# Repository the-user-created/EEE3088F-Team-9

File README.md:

# EEE3088F 2022 HAT Project

# License
[Creative Commons Attribution 4.0 International license](https://choosealicense.com/licenses/cc-by-4.0/)

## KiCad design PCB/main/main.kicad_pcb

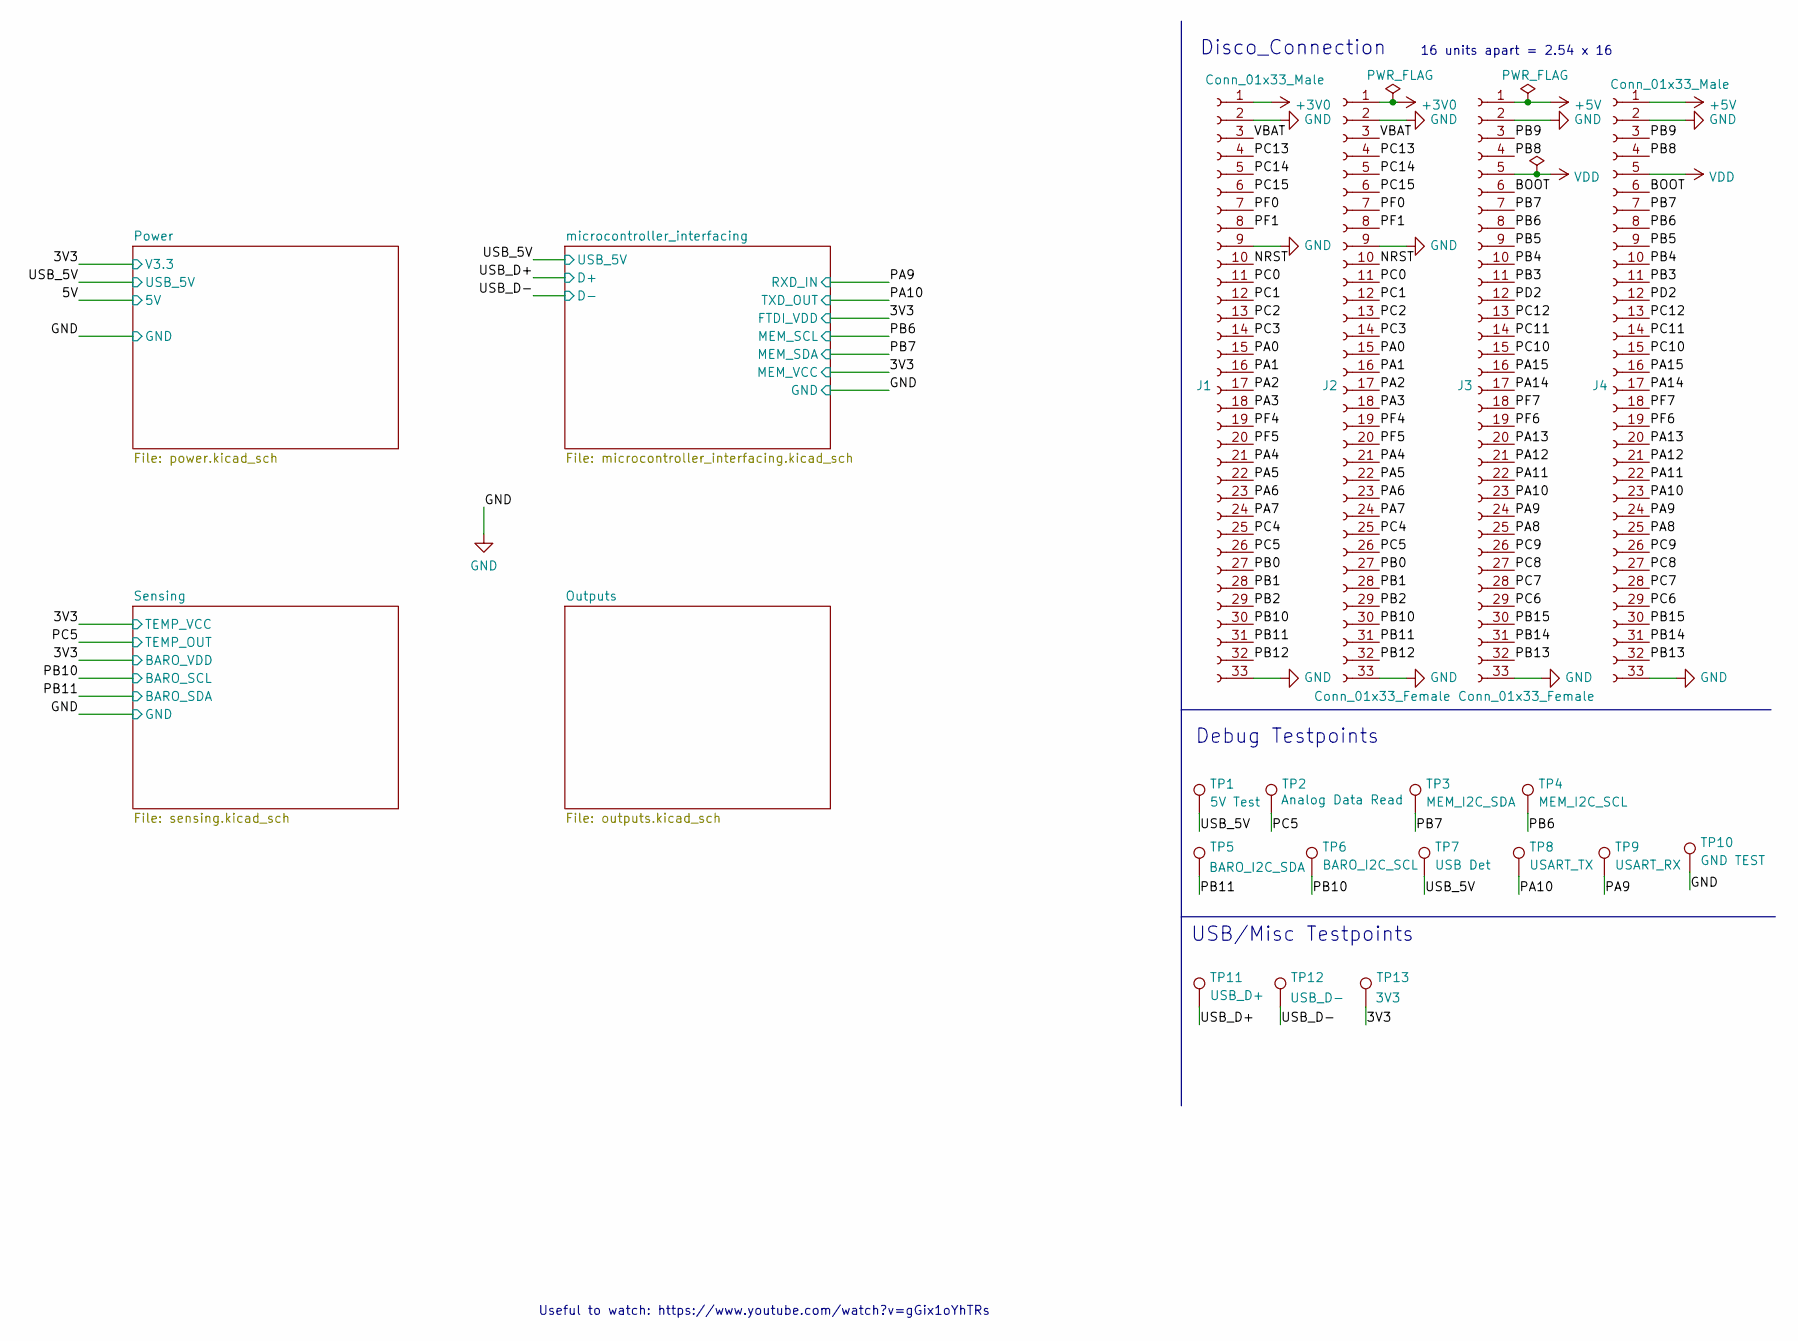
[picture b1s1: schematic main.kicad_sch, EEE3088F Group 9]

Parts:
J1, J4: Conn_01x33_Male; PinHeader_1x33_P2.54mm_Vertical
J2, J3: Conn_01x33_Female; PinSocket_1x33_P2.54mm_Vertical
TP1: 5V Test; TestPoint_Pad_2.5x2.5mm
TP2: Analog Data Read; TestPoint_Pad_2.5x2.5mm
TP3: MEM_I2C_SDA; TestPoint_Pad_2.5x2.5mm
TP4: MEM_I2C_SCL; TestPoint_Pad_2.5x2.5mm
TP5: BARO_I2C_SDA; TestPoint_Pad_2.5x2.5mm
TP6: BARO_I2C_SCL; TestPoint_Pad_2.5x2.5mm
TP7: USB Det; TestPoint_Pad_2.5x2.5mm
TP8: USART_TX; TestPoint_Pad_2.5x2.5mm
TP9: USART_RX; TestPoint_Pad_2.5x2.5mm
TP10: GND TEST; TestPoint_Pad_2.5x2.5mm
TP11: USB_D+; TestPoint_Pad_2.5x2.5mm
TP12: USB_D-; TestPoint_Pad_2.5x2.5mm
TP13: 3V3; TestPoint_Pad_2.5x2.5mm

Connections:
+3V0: J1.1, J2.1
+5V: J3.1, J4.1
/3V3: TP13.1; also elsewhere on the board
/BOOT: J3.6, J4.6
/NRST: J1.10, J2.10
/PA0: J1.15, J2.15
/PA1: J1.16, J2.16
/PA2: J1.17, J2.17
/PA3: J1.18, J2.18
/PA4: J1.21, J2.21
/PA5: J1.22, J2.22
/PA6: J1.23, J2.23
/PA7: J1.24, J2.24
/PA8: J3.25, J4.25
/PA9: J3.24, J4.24, TP9.1; also elsewhere on the board
/PA10: J3.23, J4.23, TP8.1; also elsewhere on the board
/PA11: J3.22, J4.22
/PA12: J3.21, J4.21
/PA13: J3.20, J4.20
/PA14: J3.17, J4.17
/PA15: J3.16, J4.16
/PB0: J1.27, J2.27
/PB1: J1.28, J2.28
/PB2: J1.29, J2.29
/PB3: J3.11, J4.11
/PB4: J3.10, J4.10
/PB5: J3.9, J4.9
/PB6: J3.8, J4.8, TP4.1; also elsewhere on the board
/PB7: J3.7, J4.7, TP3.1; also elsewhere on the board
/PB8: J3.4, J4.4
/PB9: J3.3, J4.3
/PB10: J1.30, J2.30, TP6.1; also elsewhere on the board
/PB11: J1.31, J2.31, TP5.1; also elsewhere on the board
/PB12: J1.32, J2.32
/PB13: J3.32, J4.32
/PB14: J3.31, J4.31
/PB15: J3.30, J4.30
/PC0: J1.11, J2.11
/PC1: J1.12, J2.12
/PC2: J1.13, J2.13
/PC3: J1.14, J2.14
/PC4: J1.25, J2.25
/PC5: J1.26, J2.26, TP2.1; also elsewhere on the board
/PC6: J3.29, J4.29
/PC7: J3.28, J4.28
/PC8: J3.27, J4.27
/PC9: J3.26, J4.26
/PC10: J3.15, J4.15
/PC11: J3.14, J4.14
/PC12: J3.13, J4.13
/PC13: J1.4, J2.4
/PC14: J1.5, J2.5
/PC15: J1.6, J2.6
/PD2: J3.12, J4.12
/PF0: J1.7, J2.7
/PF1: J1.8, J2.8
/PF4: J1.19, J2.19
/PF5: J1.20, J2.20
/PF6: J3.19, J4.19
/PF7: J3.18, J4.18
/USB_5V: TP1.1, TP7.1; also elsewhere on the board
/USB_D+: TP11.1; also elsewhere on the board
/USB_D-: TP12.1; also elsewhere on the board
/VBAT: J1.3, J2.3
GND: J1.2, J1.9, J1.33, J2.2, J2.9, J2.33, J3.2, J3.33, J4.2, J4.33, TP10.1; also elsewhere on the board
VDD: J3.5, J4.5

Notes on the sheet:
USB/Misc Testpoints
Useful to watch: https://www.youtube.com/watch?v=gGix1oYhTRs
16 units apart = 2.54 x 16
Disco_Connection
Debug Testpoints

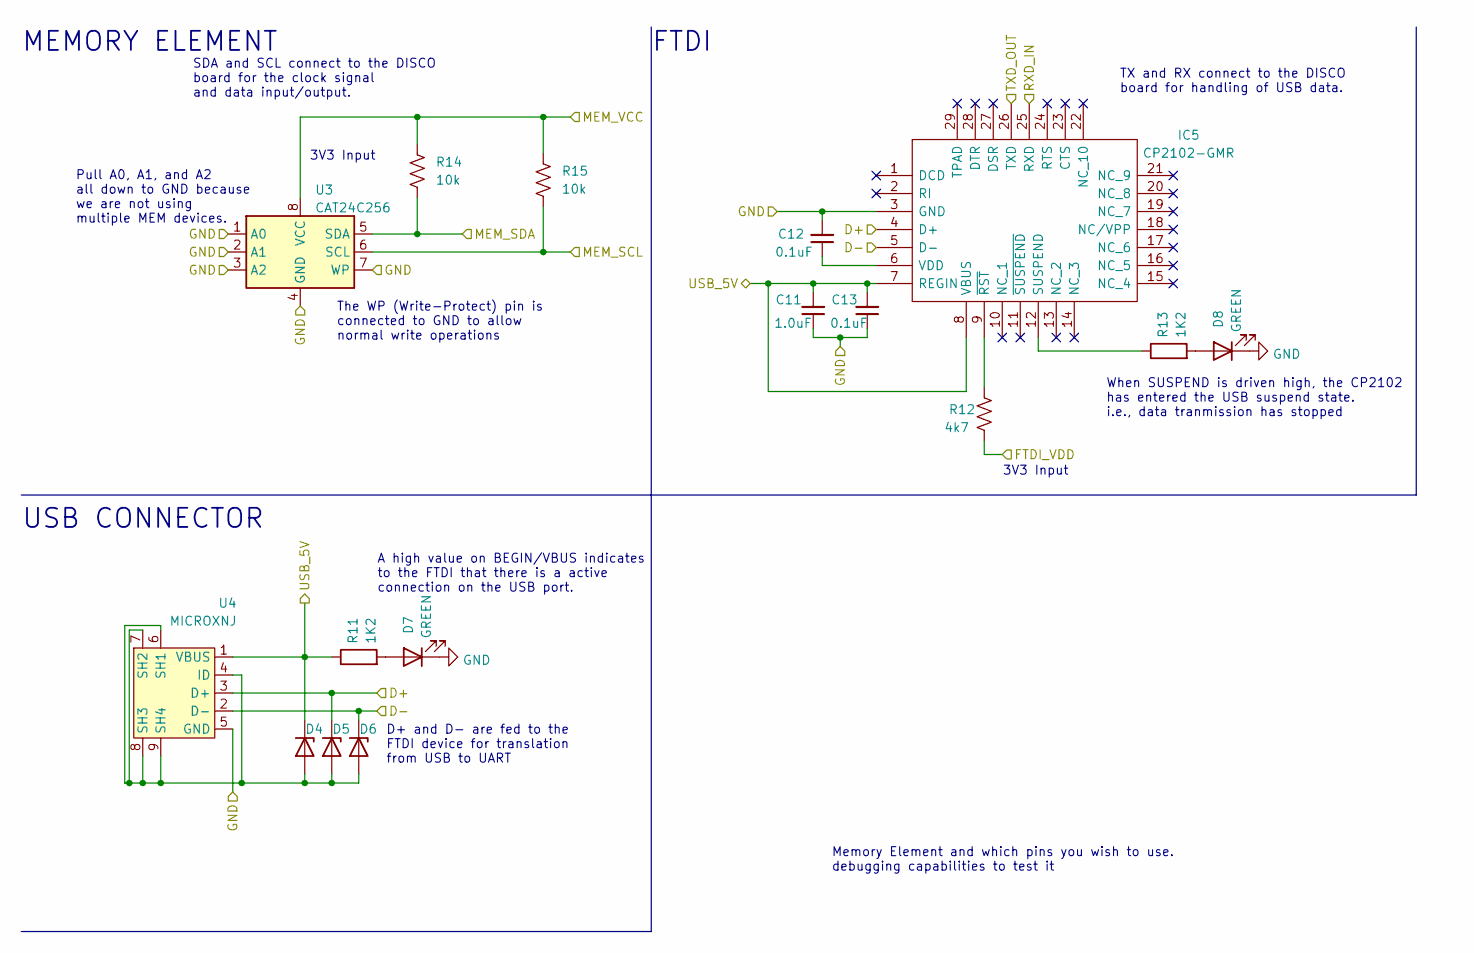
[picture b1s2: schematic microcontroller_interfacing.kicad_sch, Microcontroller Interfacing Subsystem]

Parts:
C11: 1.0uF; CAPC1608X90N; LCSC C15849
C12, C13: 0.1uF; CAPC1005X55N; LCSC C1525
D4, D5, D6: ZMMxx; LL-34_L3.5-W1.5-RD; LCSC C8056
D7, D8: GREEN; LEDC1608X50N; LCSC C72043
IC5: CP2102-GMR; QFN50P500X500X100-29N-D; Manufacturer_Part_Number CP2102-GMR; Mouser Part Number 634-CP2102-GMR
R11, R13: 1K2; RESC1608X55N; LCSC C22765
R12: 4k7; RESC1608X55N; LCSC C23162
R14, R15: 10k; R0603; LCSC C25804
U3: CAT24C256; SOIC127P600X175-8N; LCSC C6482
U4: MICROXNJ; MICRO-USB-SMD_MICROXNJ; LCSC C404969

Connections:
/3V3: R12.1, R14.1, R15.1, U3.8 (VCC); also elsewhere on the board
/PA9: IC5.25 (RXD); also elsewhere on the board
/PA10: IC5.26 (TXD); also elsewhere on the board
/PB6: R15.2, U3.6 (SCL); also elsewhere on the board
/PB7: R14.2, U3.5 (SDA); also elsewhere on the board
/USB_5V: C11.2, C13.2, D4.1 (K), IC5.7 (REGIN), IC5.8 (VBUS), R11.1, U4.1 (VBUS); also elsewhere on the board
/USB_D+: D5.1 (K), IC5.4 (D+), U4.3 (D+); also elsewhere on the board
/USB_D-: D6.1 (K), IC5.5 (D-), U4.2 (D-); also elsewhere on the board
GND: C11.1, C12.2, C13.1, D7.1 (K), D8.1 (K), IC5.3 (GND), U3.1 (A0), U3.2 (A1), U3.3 (A2), U3.4 (GND), U3.7 (WP), U4.5 (GND); also elsewhere on the board
unnamed: C12.1, IC5.6 (VDD)
unnamed: D4.2 (A), D5.2 (A), D6.2 (A), U4.4 (ID), U4.6 (SH1), U4.7 (SH2), U4.8 (SH3), U4.9 (SH4)
unnamed: D7.2 (A), R11.2
unnamed: D8.2 (A), R13.2
unnamed: IC5.9 (~RST), R12.2
unnamed: IC5.12 (SUSPEND), R13.1

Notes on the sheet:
3V3 Input
SDA and SCL connect to the DISCO board for the clock signal and data input/output.
FTDI
Pull A0, A1, and A2 all down to GND because we are not using multiple MEM devices.
MEMORY ELEMENT
The WP (Write-Protect) pin is connected to GND to allow normal write operations
TX and RX connect to the DISCO board for handling of USB data.
Memory Element and which pins you wish to use. debugging capabilities to test it
A high value on BEGIN/VBUS indicates to the FTDI that there is a active connection on the USB port.
D+ and D- are fed to the FTDI device for translation from USB to UART
When SUSPEND is driven high, the CP2102 has entered the USB suspend state. i.e., data tranmission has stopped
USB CONNECTOR

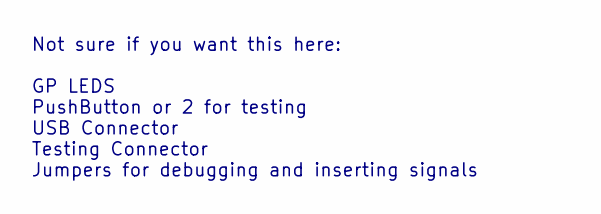
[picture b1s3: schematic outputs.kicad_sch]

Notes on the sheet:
Not sure if you want this here: GP LEDS PushButton or 2 for testing USB Connector Testing Connector Jumpers for debugging and inserting signals

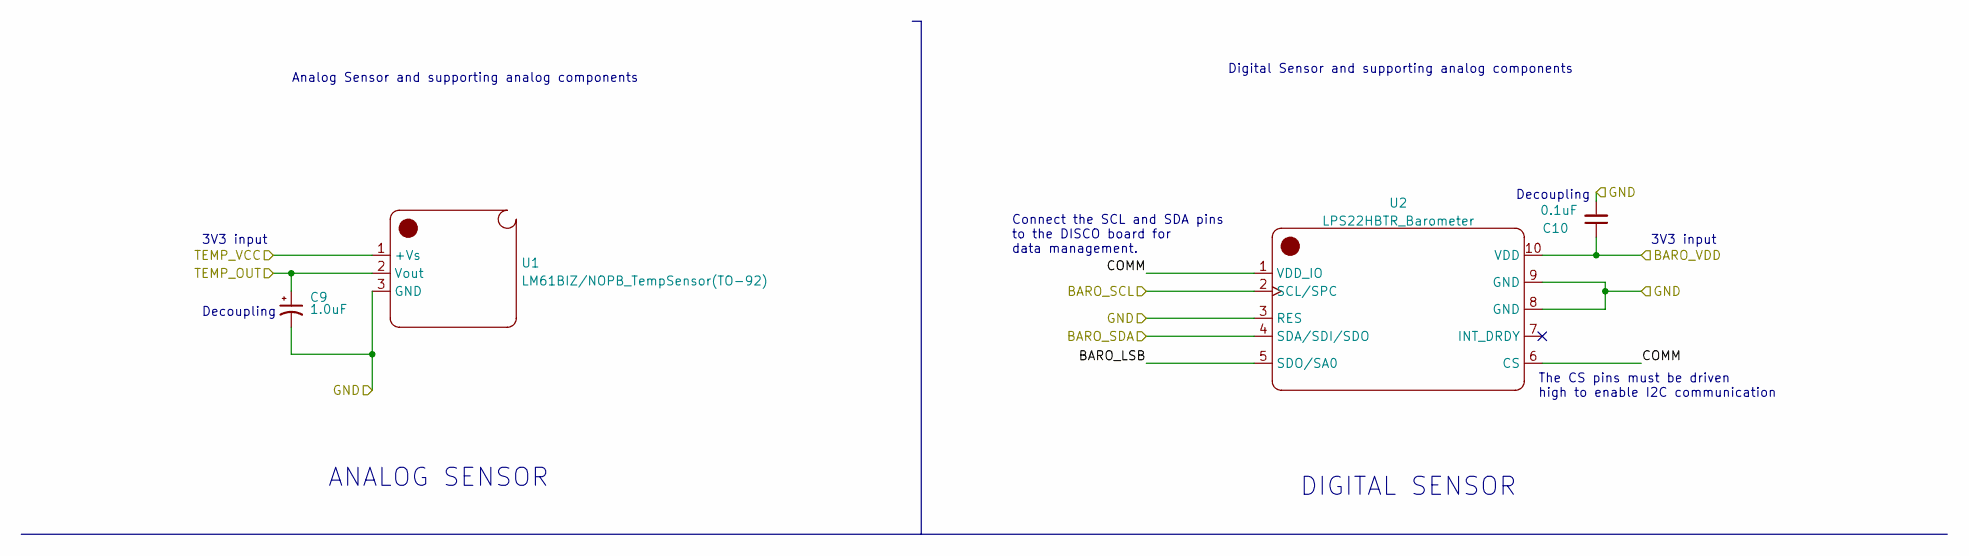
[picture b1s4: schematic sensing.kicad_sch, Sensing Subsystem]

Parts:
C9: 1.0uF; RESC1608X55N; LCSC C15849
C10: 0.1uF; CAPC1005X55N; LCSC C1525
U1: LM61BIZ/NOPB_TempSensor(TO-92); TO-92-3_L4.9-W3.7-P1.27-L; LCSC C90846
U2: LPS22HBTR_Barometer; QFN50P210X200X80-10N; LCSC C94049

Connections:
/3V3: C10.1, U1.1 (+Vs), U2.10 (VDD); also elsewhere on the board
/PB10: U2.2 (SCL/SPC); also elsewhere on the board
/PB11: U2.4 (SDA/SDI/SDO); also elsewhere on the board
/PC5: C9.1, U1.2 (Vout); also elsewhere on the board
/Sensing/BARO_LSB: U2.5 (SDO/SA0)
/Sensing/COMM: U2.1 (VDD_IO), U2.6 (CS)
GND: C9.2, C10.2, U1.3 (GND), U2.3 (RES), U2.8 (GND), U2.9 (GND); also elsewhere on the board

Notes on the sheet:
DIGITAL SENSOR
Decoupling
Analog Sensor and supporting analog components
3V3 input
ANALOG SENSOR
The CS pins must be driven high to enable I2C communication
Decoupling
Digital Sensor and supporting analog components
Connect the SCL and SDA pins to the DISCO board for data management.

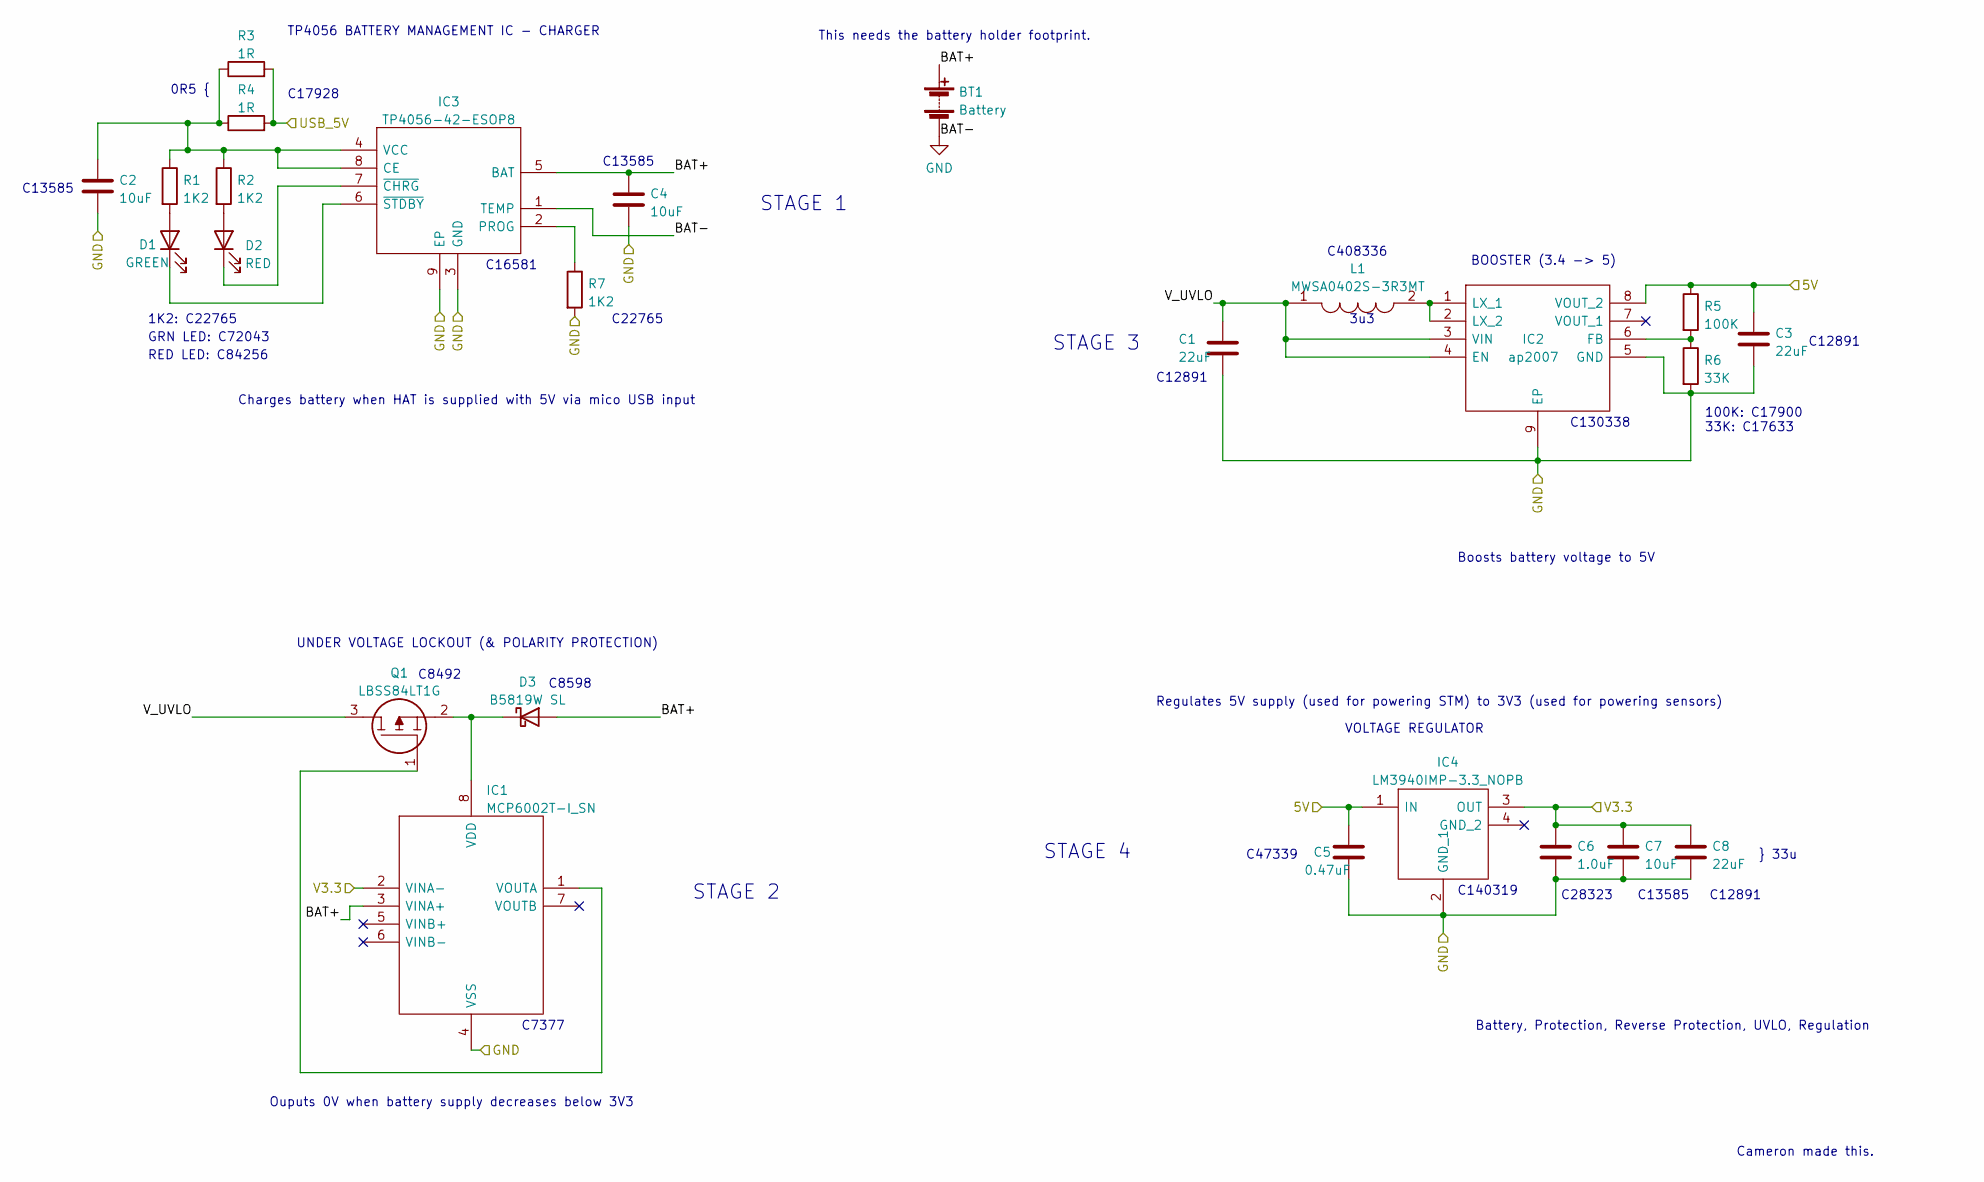
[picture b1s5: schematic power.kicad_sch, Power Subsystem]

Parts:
BT1: Battery; 18650_Holder_THT
C1, C3, C8: 22uF; CAPC3216X180N; LCSC C12891
C2, C4, C7: 10uF; CAPC3216X180N; LCSC C13585
C5: 0.47uF; CAPC1005X55N; LCSC C47339
C6: 1.0uF; CAPC1608X90N; LCSC C28323
D1: GREEN; LEDC1608X50N; LCSC C72043
D2: RED; LED0805-RD_RED; LCSC C84256
D3: B5819W SL; SOD-123_L2.7-W1.6-LS3.7-RD-1; LCSC C8598
IC1: MCP6002T-I_SN; SOIC127P600X175-8N; Manufacturer_Part_Number MCP6002T-I/SN; Mouser Part Number 579-MCP6002T-I/SN
IC2: ap2007; SOIC127P600X175-9N; Manufacturer_Part_Number ap2007; LCSC C130338
IC3: TP4056-42-ESOP8; SOIC127P600X175-9N; Manufacturer_Part_Number TP4056-42-ESOP8; LCSC C16581
IC4: LM3940IMP-3.3_NOPB; SOT230P700X180-4N; Manufacturer_Part_Number LM3940IMP-3.3/NOPB; Mouser Part Number 926-LM3940IMP3.3NOPB
L1: MWSA0402S-3R3MT; INDPM4442X200N; Manufacturer_Part_Number MWSA0402S-3R3MT; LCSC C408336
Q1: LBSS84LT1G; SOT96P237X111-3N; Manufacturer_Part_Number LBSS84LT1G; Mouser Part Number N/A
R1, R2, R7: 1K2; RESC1608X55N; LCSC C22765
R3, R4: 1R; R1206; LCSC C17928
R5: 100K; RESC3116X65N; LCSC C17900
R6: 33K; R0603; LCSC C4216

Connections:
/3V3: C6.1, C7.1, C8.1, IC1.2 (VINA-), IC4.3 (OUT); also elsewhere on the board
/5V: C3.1, C5.1, IC2.8 (VOUT_2), IC4.1 (IN), R5.1
/Power/BAT+: BT1.1 (+), C4.1, D3.2 (A), IC1.3 (VINA+), IC3.5 (BAT)
/Power/V_UVLO: C1.1, IC2.3 (VIN), IC2.4 (EN), L1.1, Q1.3
/USB_5V: R3.2, R4.2; also elsewhere on the board
GND: BT1.2 (-), C1.2, C2.2, C3.2, C4.2, C5.2, C6.2, C7.2, C8.2, IC1.4 (VSS), IC2.5 (GND), IC2.9 (EP), IC3.1 (TEMP), IC3.3 (GND), IC3.9 (EP), IC4.2 (GND_1), R6.2, R7.2; also elsewhere on the board
unnamed: C2.1, IC3.4 (VCC), IC3.8 (CE), R1.1, R2.1, R3.1, R4.1
unnamed: D1.1 (K), IC3.6 (~STDBY)
unnamed: D1.2 (A), R1.2
unnamed: D2.1 (K), IC3.7 (~CHRG)
unnamed: D2.2 (A), R2.2
unnamed: D3.1 (K), IC1.8 (VDD), Q1.2
unnamed: IC1.1 (VOUTA), Q1.1
unnamed: IC2.1 (LX_1), IC2.2 (LX_2), L1.2
unnamed: IC2.6 (FB), R5.2, R6.1
unnamed: IC3.2 (PROG), R7.1

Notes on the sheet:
C12891
STAGE 4
C17928
This needs the battery holder footprint.
C140319
BOOSTER (3.4 -> 5)
Boosts battery voltage to 5V
C8492
0R5 {
C13585
C28323
Charges battery when HAT is supplied with 5V via mico USB input
STAGE 3
STAGE 1
C22765
C408336
Ouputs 0V when battery supply decreases below 3V3
C16581
100K: C17900 33K: C17633
C130338
3u3
C47339
TP4056 BATTERY MANAGEMENT IC - CHARGER
UNDER VOLTAGE LOCKOUT (& POLARITY PROTECTION)
1K2: C22765
Battery, Protection, Reverse Protection, UVLO, Regulation
VOLTAGE REGULATOR
Regulates 5V supply (used for powering STM) to 3V3 (used for powering sensors)
RED LED: C84256
C7377
GRN LED: C72043
} 33u
Cameron made this.
STAGE 2
C8598

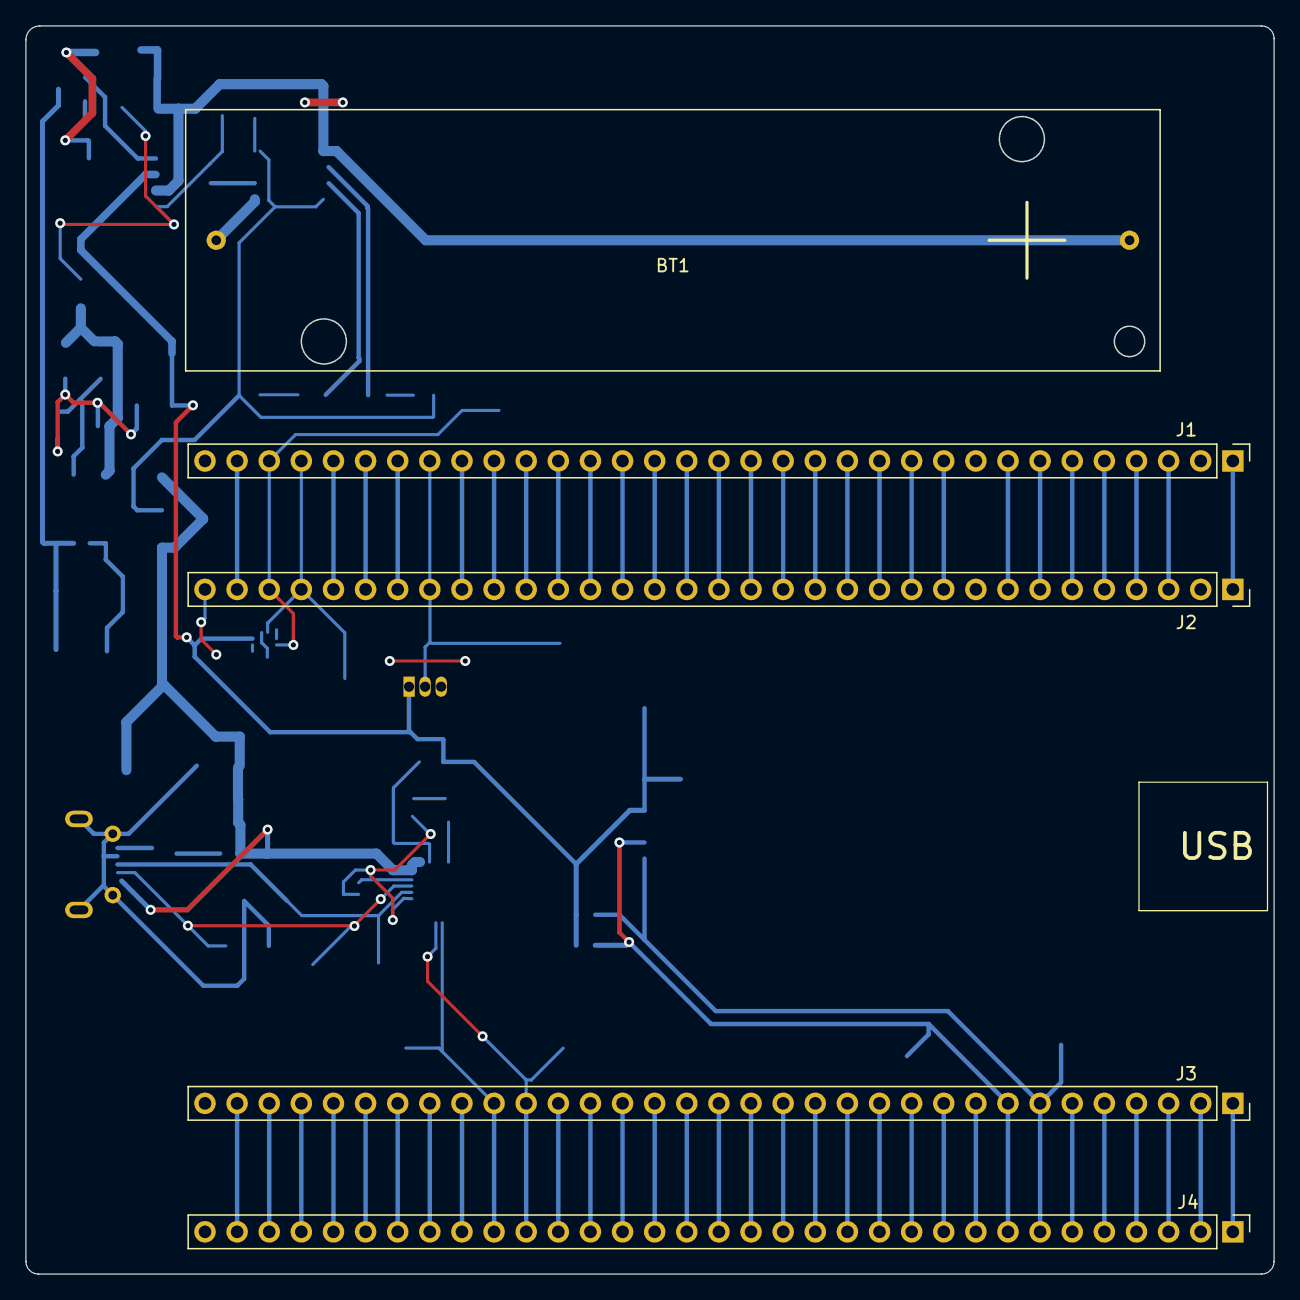
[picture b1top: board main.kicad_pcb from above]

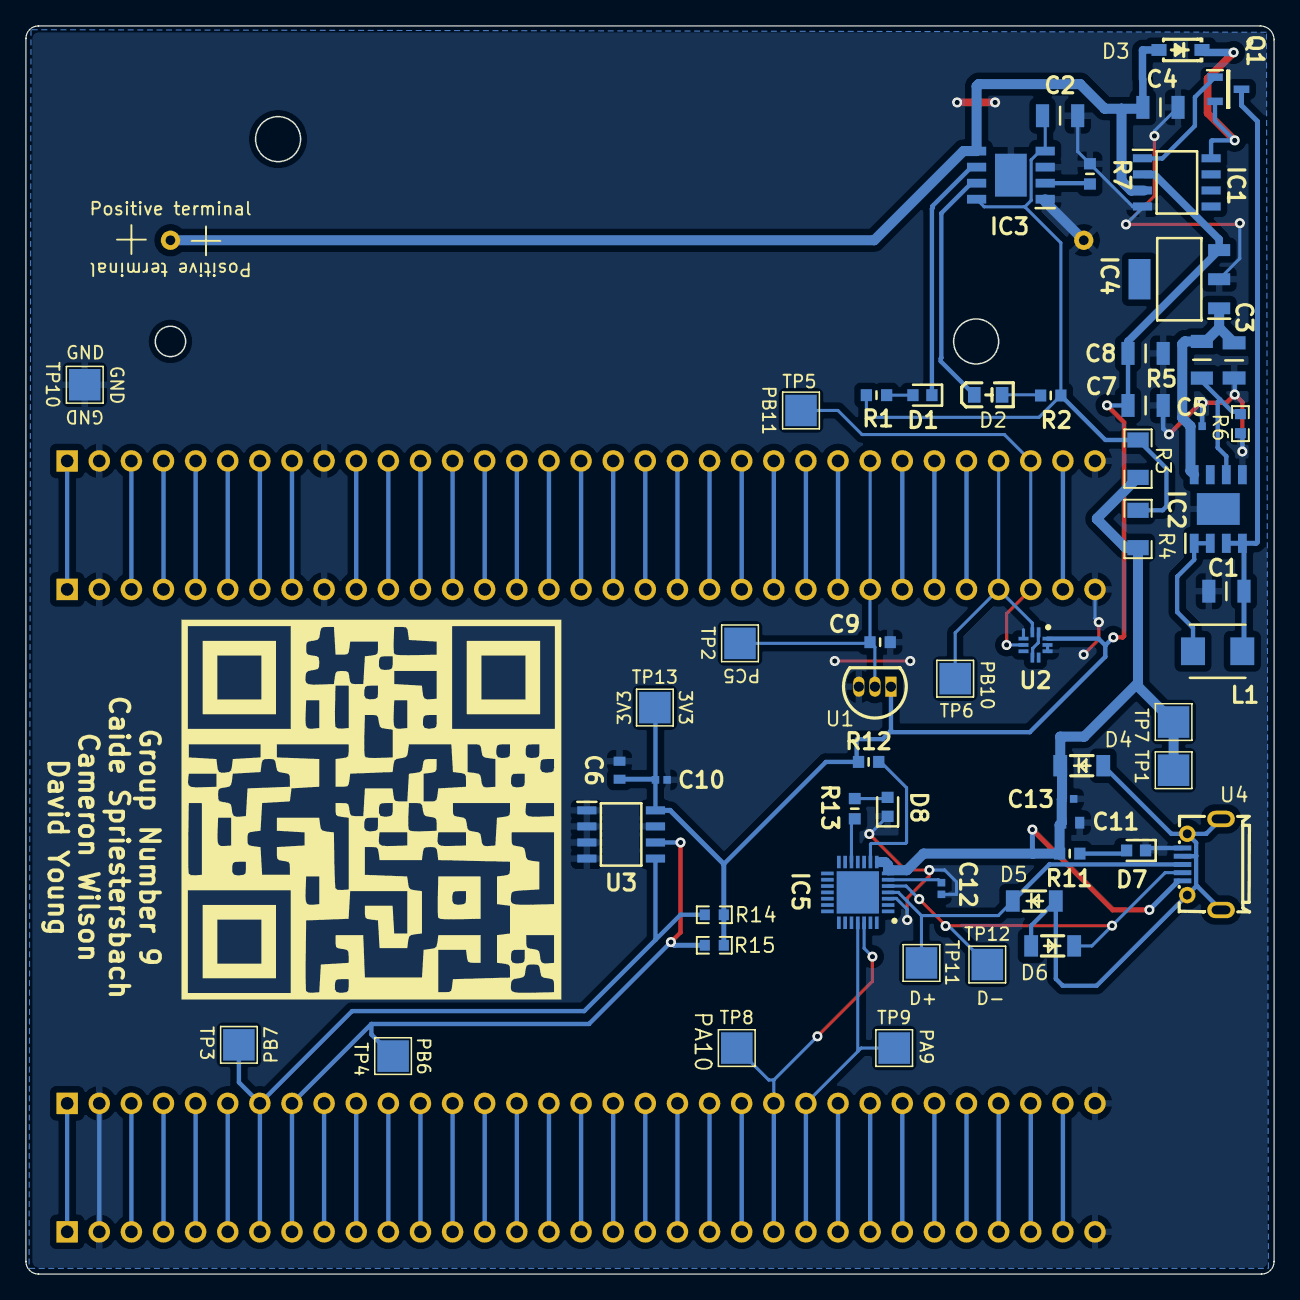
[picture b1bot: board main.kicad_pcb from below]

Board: 2 copper layers, 98.7 x 98.7 mm, 62 parts (57 on the bottom side), 86 nets.

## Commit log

2022-02-25 Added Concept Proposal
2022-02-25 Added gitignore
2022-02-25 Added LICENSE and README
2022-02-25 README fix
2022-03-04 Updated repo structure
2022-03-04 Removed proposal docs
2022-03-04 Added battery charger and polarity protection
2022-03-04 Added datasheets
2022-03-04 Added UVLO and voltage regulation
2022-03-04 Added global V3.3 label & power BOM
2022-03-04 Added most of the MC interface
2022-03-04 Added main. and power.
2022-03-04 Added Added global V3.3 label & power BOM again
2022-03-04 Added Added global V3.3 label & power BOM again again
2022-03-04 Added sensing schematic
2022-03-05 Finished v0.1 of MC Interfacing schem
2022-03-05 Adjusted .gitignore
2022-03-05 Added the sensing BOM
2022-03-11 Updated power subsystem to V0.3
2022-03-11 Added references to components
2022-03-11 Updated interfacing schem
2022-03-11 Finished initial interfacing schem
2022-03-11 Finished initial design
2022-03-11 Finished BOM
2022-03-11 some touches
2022-03-15 Fiddled a bit with labels
2022-03-16 Added Footprint and symbol files
2022-03-17 Annotated power schem, HAVE NOT ADDED INDUCTOR. v0.4
2022-03-17 Added datasheets and footprints
2022-03-17 Fixed orientation of MOSFET in UVLO. Did not add power switch due to budget. Annotated UVLO inductor. v0.4
2022-03-17 Updated all footprints of components
2022-03-17 Updated kicad_pcb file
2022-03-18 Updated labels on schematic
2022-03-19 Began PCB layout
2022-03-19 Fixed USB footprint and symbol
2022-03-19 Connected voltage supply from USB to power subsystem
2022-03-19 Completed the PCB wiring
2022-03-20 Fixed up some of the wiring on the PCB
2022-03-20 Ran ERC and DRV
2022-03-20 Finalised and generated Gerbers.
2022-03-20 Just some touches
2022-03-20 Updated power system BOM in GROUP9_BOM
2022-03-20 Nothing changed
2022-04-05 Added the contributors, the project name and revised the gradescope comments.
2022-04-05 Updated MC Interfacing with pullups
2022-04-08 Added ground to batt-
2022-04-08 Added MCP6002 OpAmp files
2022-04-08 Added thermal ground connects for batt reg and 3v3 reg. Replaced opamp with r2r opamp
2022-04-08 Updated footprints
2022-04-08 Fixed a lot of shit. Added 3 test pads. Rounded PCB corners
2022-04-08 Updated PCB with testpads
2022-04-08 Finished Gerbers and updated BOM
2022-04-08 Updated Gerbers and DNPs
2022-04-25 nothing major
2022-05-21 Added CONTRIBUTING.md
2022-05-21 Updated CONTRIBUTING.md
